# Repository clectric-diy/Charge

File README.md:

This Charge repository is where we share and develop open hardware building blocks. The idea behind a "Charge" contribution is simple: these allow us to build and test modules in smaller, reusable pieces before integrating them into larger synth designs.

These boards and supporting assets are meant to help you prototype quickly, validate circuits in manageable chunks, and assemble larger modules with more confidence.

Whether you are learning your first module design or contributing production-ready improvements, this repository is a shared design space for the clectric.diy makerspace community.

## Repository Map and Scope

- [BreakoutBoards](BreakoutBoards/): breakout boards for common UI and I/O building blocks, plus supporting design assets (KiCad files, BOMs, renders, and silkscreen resources).
- [Panels](Panels/): mechanical panel templates in AE modular sizes.
- [Protoboards](Protoboards/): perf/protoboard-style PCBs for quick prototyping.

## License (CERN-OHL-W v2)

This repository uses the CERN Open Hardware Licence v2 - Weakly Reciprocal (CERN-OHL-W).

In plain terms: you are welcome to use these files, build from them, modify them, and even sell hardware based on them.

If you share modified versions or products based on it, keep the license notices in place and share (or link to) the corresponding complete source under CERN-OHL-W.

For full legal terms, see [LICENSE](LICENSE).

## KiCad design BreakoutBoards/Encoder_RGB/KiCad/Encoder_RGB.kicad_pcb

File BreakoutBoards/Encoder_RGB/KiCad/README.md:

# Encoder + LEDs (Bourns PEL12) KiCad Files

KiCad source files for the encoder + RGB breakout.

## Key Files

- `Encoder_RGB.kicad_sch`: schematic (title block: "Charge Encoder w/ RGB LED").
- `Encoder_RGB.kicad_pcb`: PCB layout.
- `Encoder_RGB.kicad_pro`: project configuration.
- `Encoder_RGB.kicad_prl`: local project state.

## Components

BOM and manufacturer part numbers will be listed here as this breakout board is developed.

- Encoder: Bourns PEL12
- LEDs: TBD
- Current limiting resistors: TBD
- Connector / pin header: TBD

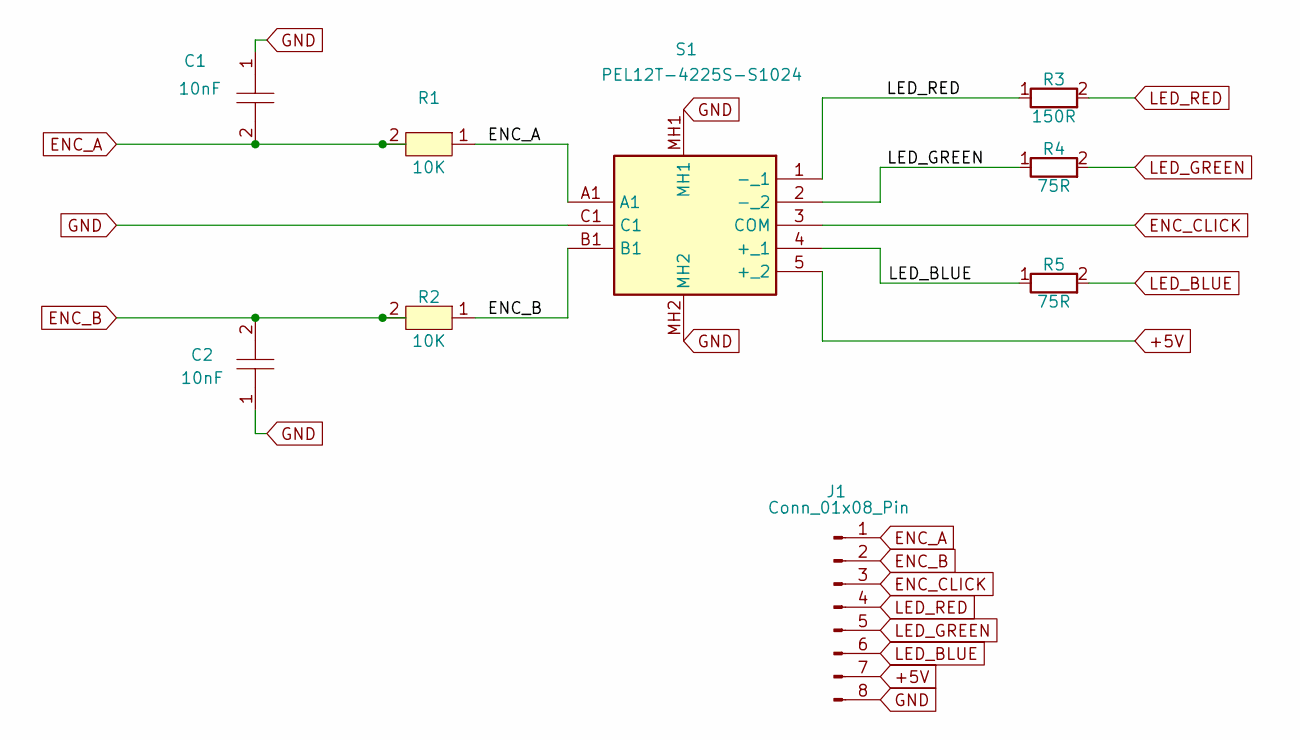
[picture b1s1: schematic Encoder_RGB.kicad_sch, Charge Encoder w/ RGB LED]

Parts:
C1, C2: 10nF; C0603
J1: Conn_01x08_Pin; PinHeader_1x08_P2.54mm_Vertical
R1, R2: 10K; R0603
R3: 150R; R0603
R4, R5: 75R; R0603
S1: PEL12T-4225S-S1024; PEL12T4225SS1024; Mouser Part Number 652-PEL12T4225SS1024

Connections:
+5V: J1.7, S1.5 (+_2)
ENC_A: C1.2, J1.1, R1.1, R1.2, S1.A1
ENC_B: C2.2, J1.2, R2.1, R2.2, S1.B1
ENC_CLICK: J1.3, S1.3 (COM)
GND: C1.1, C2.1, J1.8, S1.C1, S1.MH1, S1.MH2
LED_BLUE: J1.6, R5.1, R5.2, S1.4 (+_1)
LED_GREEN: J1.5, R4.1, R4.2, S1.2 (-_2)
LED_RED: J1.4, R3.1, R3.2, S1.1 (-_1)

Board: 2 copper layers, 9 parts (1 on the bottom side), 8 nets, no tracks yet.

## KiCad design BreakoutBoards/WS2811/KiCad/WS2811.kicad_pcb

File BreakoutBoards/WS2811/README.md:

# WS2811 Breakout

Breakout board for a WS2811-based single RGB LED driver stage (NeoPixel-style control of a discrete RGB LED).

## Purpose

Enable serially controlled RGB lighting with a discrete LED and WS2811 driver as a reusable building block.

## Contents

- [KiCad](KiCad/): schematic and PCB source for the WS2811 breakout.

## Components

BOM and manufacturer part numbers will be listed here as this breakout board is developed.

- WS2811 LED driver IC: TBD
- RGB LED: TBD
- Current limiting resistors: TBD
- Connector / pin header: TBD

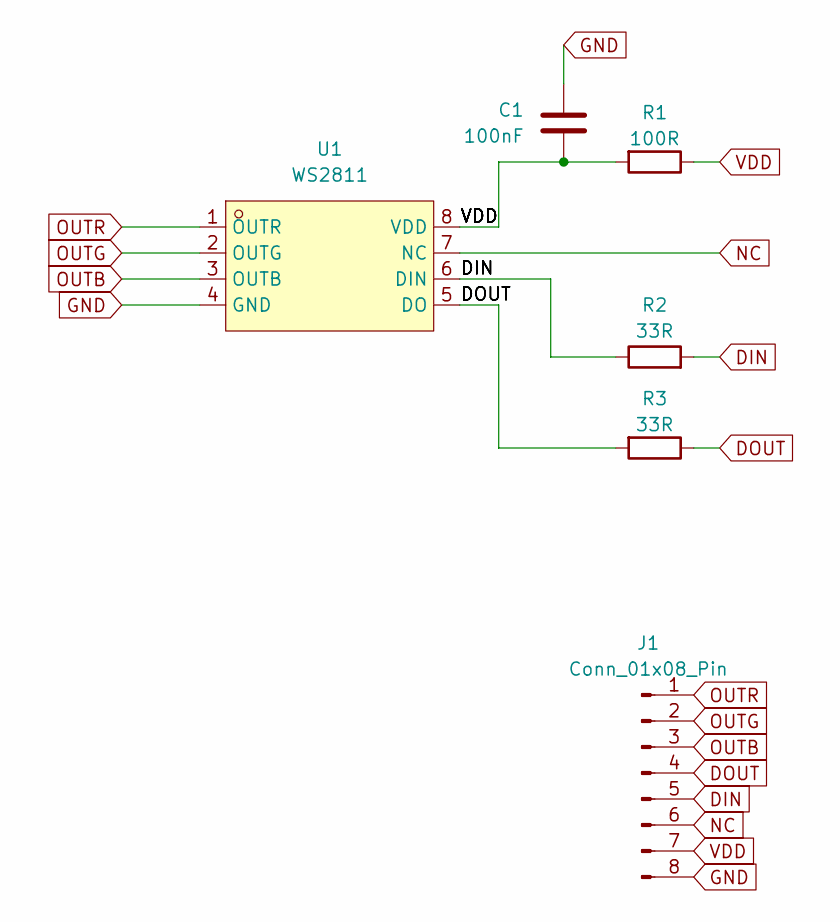
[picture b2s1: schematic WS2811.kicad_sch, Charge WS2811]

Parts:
C1: 100nF; C_0402_1005Metric
J1: Conn_01x08_Pin; PinHeader_1x08_P2.54mm_Vertical
R1: 100R; R_0402_1005Metric
R2, R3: 33R; R_0402_1005Metric
U1: WS2811; SOP-8_L4.9-W3.9-P1.27-LS6.0-BL; LCSC Part C114581

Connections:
DIN: J1.5, R2.1, R2.2, U1.6 (DIN)
DOUT: J1.4, R3.1, R3.2, U1.5 (DO)
GND: C1.1, J1.8, U1.4 (GND)
NC: J1.6, U1.7 (NC)
OUTB: J1.3, U1.3 (OUTB)
OUTG: J1.2, U1.2 (OUTG)
OUTR: J1.1, U1.1 (OUTR)
VDD: C1.2, J1.7, R1.1, R1.2, U1.8 (VDD)

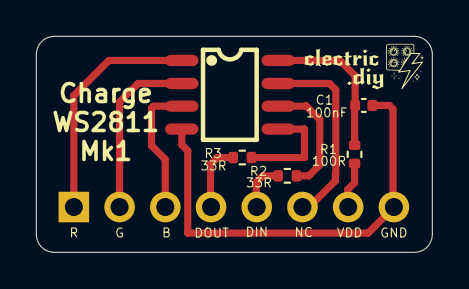
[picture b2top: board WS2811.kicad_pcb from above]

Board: 2 copper layers, 22.0 x 12.0 mm, 6 parts (1 on the bottom side), 8 nets.

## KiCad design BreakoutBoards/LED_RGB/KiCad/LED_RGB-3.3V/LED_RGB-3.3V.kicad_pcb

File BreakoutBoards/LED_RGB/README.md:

# 3.3V RGB LED Breakout

Breakout board for driving/using an RGB LED at 3.3V logic/power levels.

## Purpose

Offer a simple RGB indication module for 3.3V systems where color status or feedback is needed.

## Contents

- [KiCad](KiCad/): project container for the LED breakout design.

## Components

BOM and manufacturer part numbers will be listed here as this breakout board is developed.

- RGB LED (3.3V usage context): TBD
- Current limiting resistors: TBD
- Connector / pin header: TBD

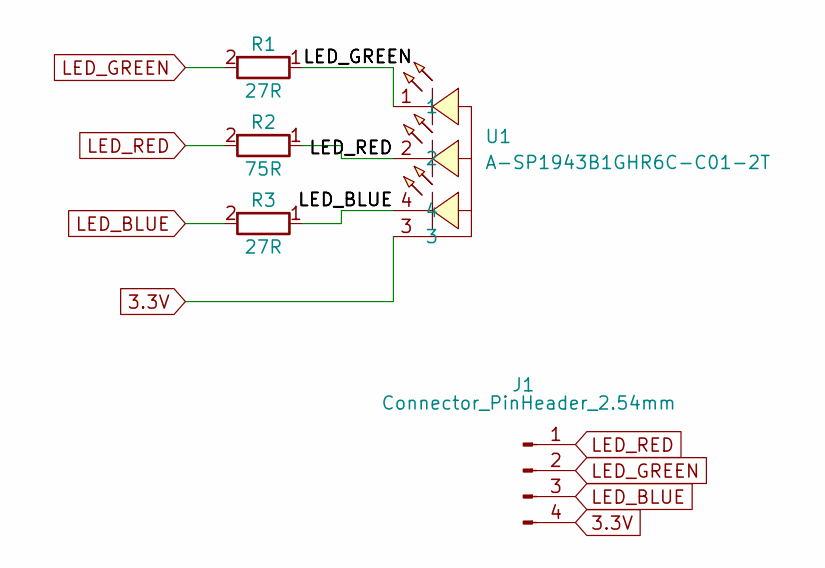
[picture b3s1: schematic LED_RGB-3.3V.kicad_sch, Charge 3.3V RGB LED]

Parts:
J1: Connector_PinHeader_2.54mm; PinHeader_1x04_P2.54mm_Vertical
R1, R3: 27R; R0603
R2: 75R; R0603
U1: A-SP1943B1GHR6C-C01-2T; LED-SMD_4P-L1.6-W1.5-BL_A-SP1943B1GHR6C-C01-2T; LCSC Part C19171342

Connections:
3.3V: J1.4, U1.3
LED_BLUE: J1.3, R3.1, R3.2, U1.4
LED_GREEN: J1.2, R1.1, R1.2, U1.1
LED_RED: J1.1, R2.1, R2.2, U1.2

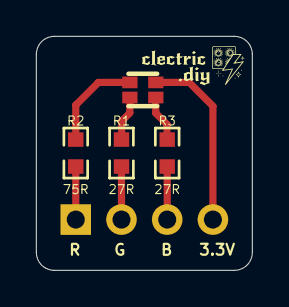
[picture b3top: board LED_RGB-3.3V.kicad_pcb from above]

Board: 2 copper layers, 12.0 x 13.0 mm, 5 parts (1 on the bottom side), 4 nets.

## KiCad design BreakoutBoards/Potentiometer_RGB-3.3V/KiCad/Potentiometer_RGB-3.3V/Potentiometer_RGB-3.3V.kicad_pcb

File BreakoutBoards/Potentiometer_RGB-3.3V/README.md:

# Potentiometer + RGB (3.3V) Breakout

Combined control module that pairs a potentiometer interface with an integrated 3.3V RGB LED section.

## Purpose

Combine analog control and visual state indication on one breakout to reduce wiring and panel footprint in UI-heavy builds.

## Contents

- [KiCad](KiCad/): project container for the combined potentiometer/RGB breakout.

## Components

BOM and manufacturer part numbers will be listed here as this breakout board is developed.

- Potentiometer: TBD
- RGB LED: TBD
- Current limiting resistors: TBD
- Connector / pin header: TBD

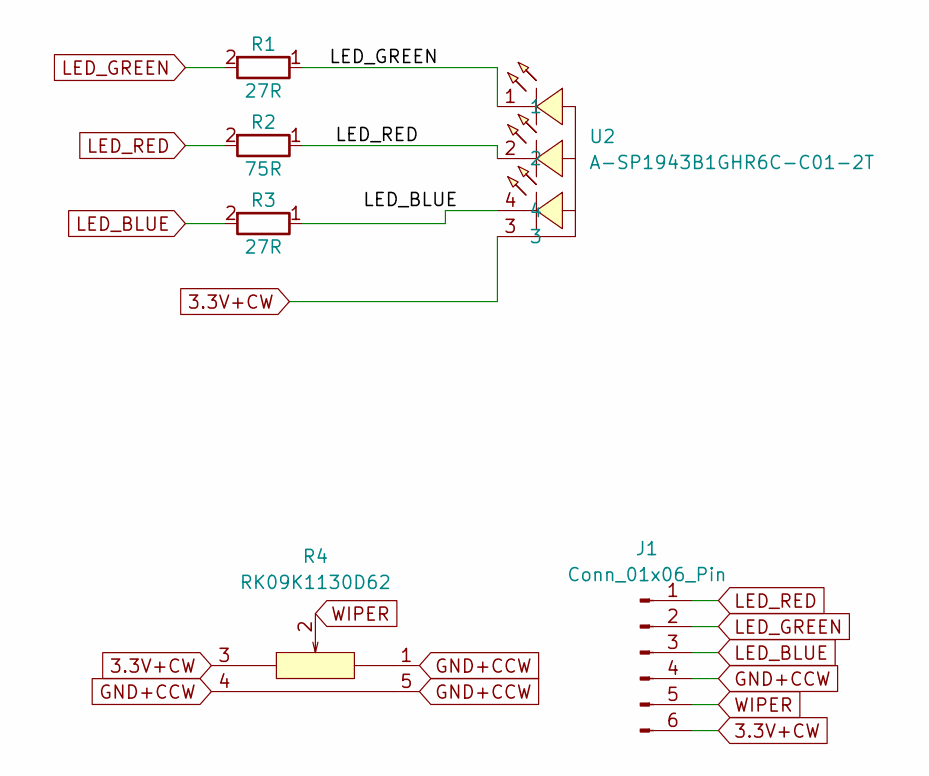
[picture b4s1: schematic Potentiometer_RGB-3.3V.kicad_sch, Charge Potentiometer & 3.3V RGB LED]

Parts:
J1: Conn_01x06_Pin; PinHeader_1x06_P2.54mm_Vertical
R1, R3: 27R; R0603
R2: 75R; R0603
R4: RK09K1130D62; RES-TH_RK09K113004U; LCSC Part C470294
U2: A-SP1943B1GHR6C-C01-2T; LED-SMD_4P-L1.6-W1.5-BL_A-SP1943B1GHR6C-C01-2T; LCSC Part C19171342

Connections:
3.3V+CW: J1.6, R4.3, U2.3
GND+CCW: J1.4, R4.1, R4.4 (EH), R4.5 (EH)
LED_BLUE: J1.3, R3.1, R3.2, U2.4
LED_GREEN: J1.2, R1.1, R1.2, U2.1
LED_RED: J1.1, R2.1, R2.2, U2.2
WIPER: J1.5, R4.2

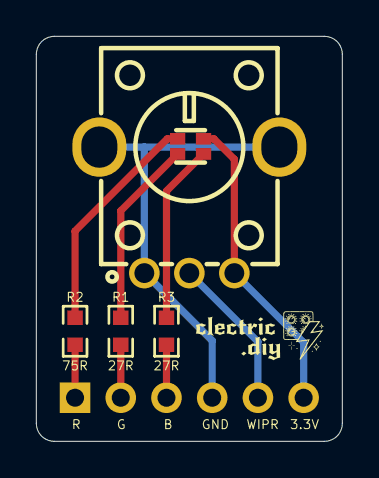
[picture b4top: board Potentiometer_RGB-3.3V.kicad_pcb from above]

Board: 2 copper layers, 17.0 x 22.5 mm, 6 parts (1 on the bottom side), 6 nets.

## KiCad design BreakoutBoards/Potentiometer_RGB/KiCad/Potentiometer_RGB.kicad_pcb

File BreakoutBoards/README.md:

# Breakout Boards

This directory contains small, focused hardware modules for common controls and interfaces used in synth and embedded builds.

## Modules

- [DaisySeed](DaisySeed/): a carrier for the Daisy Seed module, which is the main microcontroller "brain" that runs your synth code and controls everything else.
- [Encoder](Encoder/): rotary knob input module; an encoder lets you turn endlessly to move through values, menus, or parameters.
- [Encoder_RGB](Encoder_RGB/): rotary encoder plus RGB LEDs; you get one control that can both adjust settings and show visual state by color.
- [LED_RGB](LED_RGB/): RGB indicator light module for 3.3V systems; useful for showing mode, status, level ranges, or activity.
- [MicroSD](MicroSD/): storage interface module; a microSD breakout lets your project read/write files like presets, samples, or logs.
- [Potentiometer](Potentiometer/): classic analog knob input; a potentiometer gives a direct position value (for example 0-100%).
- [Potentiometer_RGB-3.3V](Potentiometer_RGB-3.3V/): potentiometer plus RGB LED in one module, combining hands-on control with immediate visual feedback.
- [USB_TypeC](USB_TypeC/): general USB Type-C connection module for bringing power and, when designed in, USB data into your project.
- [USB_TypeC_PowerOnly](USB_TypeC_PowerOnly/): simplified USB Type-C power-input module when you only need power, not USB data.
- [WS2811](WS2811/): addressable LED driver module; WS2811 lets a controller set LED color with a serial data signal (NeoPixel-style behavior).

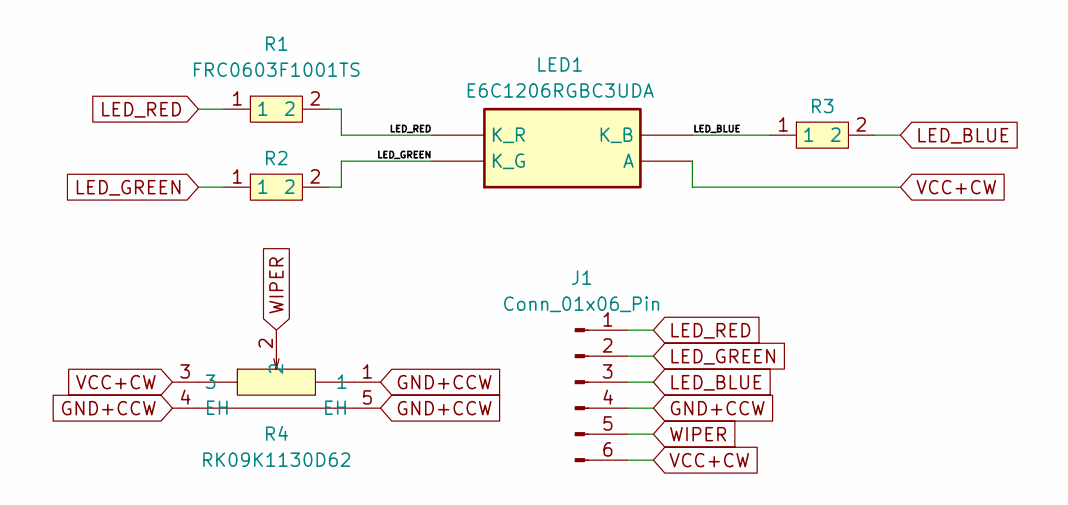
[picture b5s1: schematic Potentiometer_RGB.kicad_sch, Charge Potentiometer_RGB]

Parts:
J1: Conn_01x06_Pin; HDR-TH_6P-P2.54-V-M-1
LED1: E6C1206RGBC3UDA; Manufacturer_Part_Number E6C1206RGBC3UDA
R1, R2, R3: FRC0603F1001TS; R0603; LCSC Part C2907002
R4: RK09K1130D62; RES-TH_RK09K113004U; LCSC Part C470294

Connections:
GND+CCW: J1.4, R4.1, R4.4 (EH), R4.5 (EH)
LED_BLUE: J1.3, LED1.4 (K_B), R3.1, R3.2
LED_GREEN: J1.2, LED1.1 (K_G), R2.1, R2.2
LED_RED: J1.1, LED1.3 (K_R), R1.1, R1.2
VCC+CW: J1.6, LED1.2 (A), R4.3
WIPER: J1.5, R4.2

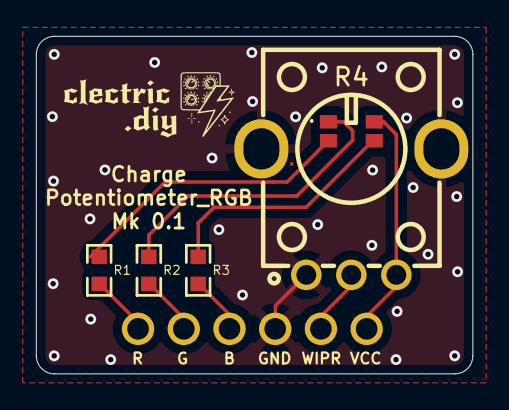
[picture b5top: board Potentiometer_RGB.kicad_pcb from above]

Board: 2 copper layers, 24.2 x 18.8 mm, 6 parts (1 on the bottom side), 6 nets.

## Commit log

2026-02-20 added sponsorship button
2026-02-20 added CERN OHL-W license
2026-02-20 setup github pages config
2026-02-20 ignoring macOS and KiCad working files
2026-02-20 ignoring kicad working files
2026-02-20 Mk 0.1 version of LED_RGB
2026-02-20 ignoring fabrication plugin files
2026-02-20 tweaked silkscreen positions
2026-02-21 created Potentiometer Mk 0.1
2026-02-21 created Potentiometer_RGB Mk 0.1
2026-02-21 removing content duplicated in description
2026-02-22 ran DRC and resolved issues
2026-02-22 description of NeoPixel integration board
2026-02-22 seperating potentiometer and WS2811 boards
2026-02-22 seperating encoder and WS2811 boards
2026-02-22 removing resistors to make more versatile and selecting new led to use
2026-02-23 renamed to specify voltage
2026-02-23 updated to Mk1 and sent for manufacturing
2026-02-28 ignoring backup copies
2026-02-28 created models to generate .step files
2026-03-28 consolidating "Charge" elements
2026-04-07 vibed with CoPilot on READMEs to explain the avalable and planned assets.
2026-04-07 removed redundant section
2026-04-08 I have renamed to remove the 3.3V spec to accept other Vcc. I will update the resistors to accomodate.
2026-04-08 Initial design for a beginner-friendly ATmega4809 breakout board
    Planning to add safety features, including a resettable fuse and a protection diode, to keep the board safe from accidental short circuits or plugging in batteries backward.
    Planning to simplify wiring to handle the "boring" stuff behind the scenes by connecting all power and ground pins together on the board so users don't have to.
    Planning a built-in USB connection and auto-reset circuit so novices can upload code directly from the Arduino IDE without extra hardware.
    Labeling ports (like PA0, PB1) to help new users learn the real chip layout while building their projects.
2026-04-08 further restructuring the separation of Potentiometer_RGB from Potentiometer
2026-04-26 renaming and reorganizing to clarify use

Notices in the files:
BreakoutBoards/Encoder_RGB/KiCad/Encoder_RGB.kicad_pcb:
Copyright © 2026 clectric.diy Licensed under CERN-OHL-W v2
